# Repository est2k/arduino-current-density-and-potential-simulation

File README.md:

# arduino-current-density-and-potential-simulation
Potential and Current Density Simulation of Arduino Uno using FreeCAD, ElmerFEM and ParaView

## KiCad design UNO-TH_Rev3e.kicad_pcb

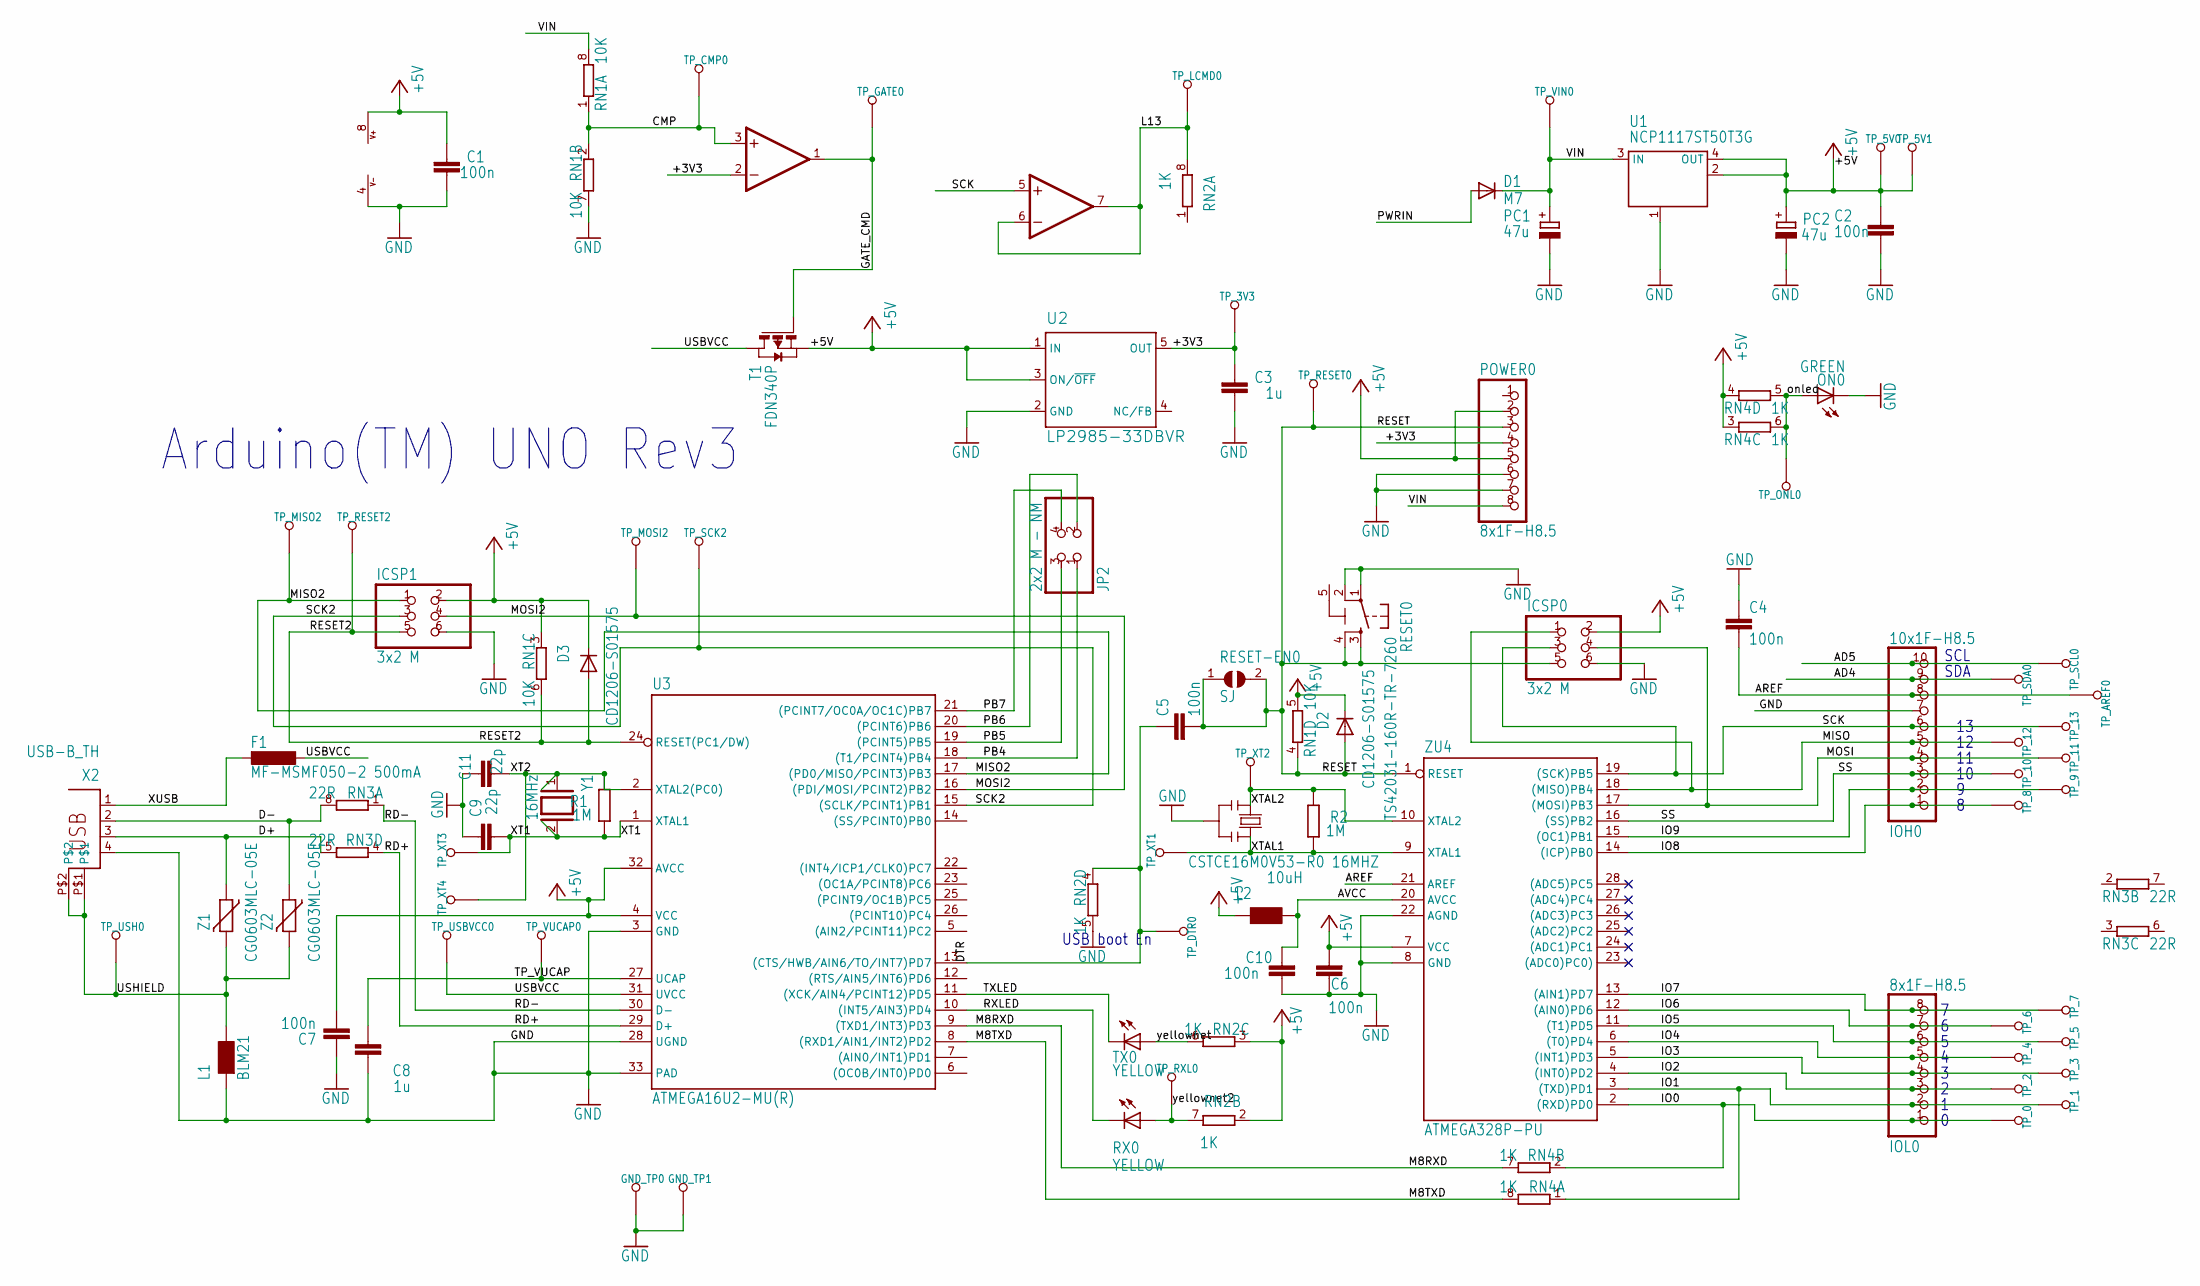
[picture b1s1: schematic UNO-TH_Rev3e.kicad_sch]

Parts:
C1, C2, C4, C5, C6, C7, C10: 100n; C0603-ROUND
C3, C8: 1u; C0603-ROUND
C9, C11: 22p; C0603-ROUND
D1: M7; SMB
D2, D3: CD1206-S01575; MINIMELF
F1: MF-MSMF050-2 500mA; L1812
GND_TP0, GND_TP1: TP_SP; TP-SP
ICSP0, ICSP1: 3x2 M; 2X03
IOH0: 10x1F-H8.5; 1X10
IOL0: 8x1F-H8.5; 1X08
JP2: 2x2 M - NM; 2X02
L1: BLM21; 0805
L2: 10uH; 0805
ON0: GREEN; CHIP-LED0805
PC1, PC2: 47u; PANASONIC_D
POWER0: 8x1F-H8.5; 1X08
R1, R2: 1M; R0603-ROUND
RESET0: TS42031-160R-TR-7260; TS42
RESET-EN0: SJ
RN1: 10K; CAY16
RN2, RN4: 1K; CAY16
RN3: 22R; CAY16
RX0: YELLOW; CHIP-LED0805
T1: FDN340P; SOT-23
TP_0, TP_1, TP_2, TP_3, TP_3V3, TP_4, TP_5, TP_5V0, TP_5V1, TP_6, TP_7, TP_8, TP_9, TP_10, TP_11, TP_12, TP_13: TP_SP; TP-SP
TP_AREF0: TP_SP; TP-SP
TP_CMP0: TP_SP; TP-SP
TP_DTR0: TP_SP; TP-SP
TP_GATE0: TP_SP; TP-SP
TP_LCMD0: TP_SP; TP-SP
TP_MISO2: TP_SP; TP-SP
TP_MOSI2: TP_SP; TP-SP
TP_ONL0: TP_SP; TP-SP
TP_RESET0, TP_RESET2: TP_SP; TP-SP
TP_RXL0: TP_SP; TP-SP
TP_SCK2: TP_SP; TP-SP
TP_SCL0: TP_SP; TP-SP
TP_SDA0: TP_SP; TP-SP
TP_USBVCC0: TP_SP; TP-SP
TP_USH0: TP_SP; TP-SP
TP_VIN0: TP_SP; TP-SP
TP_VUCAP0: TP_SP; TP-SP
TP_XT1, TP_XT2, TP_XT3, TP_XT4: TP_SP; TP-SP
TX0: YELLOW; CHIP-LED0805
U1: NCP1117ST50T3G; SOT223
U2: LP2985-33DBVR; SOT23-DBV
U3: ATMEGA16U2-MU(R); MLF32
U5: LMV358IDGKR; MSOP08
X2: USB-B_TH; PN61729
Y1: 16MHz; QS
Y2: CSTCE16M0V53-R0 16MHZ; RESONATOR
Z1, Z2: CG0603MLC-05E; CT_CN0603
ZU4: ATMEGA328P-PU; DIL28-3

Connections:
+5V: C1.2, C2.2, C6.2, C7.1, D2.C, D3.C, ICSP0.2, ICSP1.2, L2.1, PC2.+, POWER0.2, POWER0.5, RN1.3 (1), RN1.5 (2), RN2.2 (1), RN2.3 (1), RN4.3 (1), RN4.4 (1), T1.2 (S), TP_5V0.X (TESTP), TP_5V1.X (TESTP), U1.2 (OUT@1), U1.4 (OUT), U2.1 (IN), U2.3 (ON/~OFF), U3.4 (VCC), U3.32 (AVCC), U5.8 (V+), ZU4.7 (VCC)
/+3V3: C3.2, POWER0.4, TP_3V3.X (TESTP), U2.5 (OUT), U5.2 (-IN)
/AD4: IOH0.9, TP_SDA0.X (TESTP)
/AD5: IOH0.10, TP_SCL0.X (TESTP)
/AREF: C4.2, IOH0.8, TP_AREF0.X (TESTP), ZU4.21 (AREF)
/AVCC: C10.2, L2.2, ZU4.20 (AVCC)
/CMP: RN1.1, RN1.2 (1), TP_CMP0.X (TESTP), U5.3 (+IN)
/D+: RN3.5 (2), X2.3, Z1.1
/D-: RN3.8 (2), X2.2, Z2.1
/DTR: C5.1, RN2.4 (1), TP_DTR0.X (TESTP), U3.13 ((CTS/HWB/AIN6/TO/INT7)PD7)
/GATE_CMD: T1.3 (G), TP_GATE0.X (TESTP), U5.1 (OUT)
/IO0: IOL0.1, RN4.2 (1), TP_0.X (TESTP), ZU4.2 ((RXD)PD0)
/IO1: IOL0.2, RN4.1, TP_1.X (TESTP), ZU4.3 ((TXD)PD1)
/IO2: IOL0.3, TP_2.X (TESTP), ZU4.4 ((INT0)PD2)
/IO3: IOL0.4, TP_3.X (TESTP), ZU4.5 ((INT1)PD3)
/IO4: IOL0.5, TP_4.X (TESTP), ZU4.6 ((T0)PD4)
/IO5: IOL0.6, TP_5.X (TESTP), ZU4.11 ((T1)PD5)
/IO6: IOL0.7, TP_6.X (TESTP), ZU4.12 ((AIN0)PD6)
/IO7: IOL0.8, TP_7.X (TESTP), ZU4.13 ((AIN1)PD7)
/IO8: IOH0.1, TP_8.X (TESTP), ZU4.14 ((ICP)PB0)
/IO9: IOH0.2, TP_9.X (TESTP), ZU4.15 ((OC1)PB1)
/L13: RN2.8 (2), TP_LCMD0.X (TESTP), U5.6 (-IN), U5.7 (OUT)
/M8RXD: RN4.7 (2), U3.9 ((TXD1/INT3)PD3)
/M8TXD: RN4.8 (2), U3.8 ((RXD1/AIN1/INT2)PD2)
/MISO: ICSP0.1, IOH0.5, TP_12.X (TESTP), ZU4.18 ((MISO)PB4)
/MISO2: ICSP1.1, TP_MISO2.X (TESTP), U3.17 ((PD0/MISO/PCINT3)PB3)
/MOSI: ICSP0.4, IOH0.4, TP_11.X (TESTP), ZU4.17 ((MOSI)PB3)
/MOSI2: ICSP1.4, TP_MOSI2.X (TESTP), U3.16 ((PDI/MOSI/PCINT2)PB2)
/PB4: JP2.1, U3.18 ((T1/PCINT4)PB4)
/PB5: JP2.3, U3.19 ((PCINT5)PB5)
/PB6: JP2.2, U3.20 ((PCINT6)PB6)
/PB7: JP2.4, U3.21 ((PCINT7/OC0A/OC1C)PB7)
/PWRIN: D1.A
/RD+: RN3.4 (1), U3.29 (D+)
/RD-: RN3.1, U3.30 (D-)
/RESET: C5.2, D2.A, ICSP0.5, POWER0.3, RESET0.3, RESET0.4, RESET-EN0.1, RESET-EN0.2, RN1.4 (1), TP_RESET0.X (TESTP), ZU4.1 (RESET)
/RESET2: D3.A, ICSP1.5, RN1.6 (2), TP_RESET2.X (TESTP), U3.24 (RESET(PC1/DW))
/RXLED: RX0.C, U3.10 ((INT5/AIN3)PD4)
/SCK: ICSP0.3, IOH0.6, TP_13.X (TESTP), U5.5 (+IN), ZU4.19 ((SCK)PB5)
/SCK2: ICSP1.3, TP_SCK2.X (TESTP), U3.15 ((SCLK/PCINT1)PB1)
/SS: IOH0.3, TP_10.X (TESTP), ZU4.16 ((SS)PB2)
/TP_VUCAP: C8.1, TP_VUCAP0.X (TESTP), U3.27 (UCAP)
/TXLED: TX0.C, U3.11 ((XCK/AIN4/PCINT12)PD5)
/USBVCC: F1.1, T1.1 (D), TP_USBVCC0.X (TESTP), U3.31 (UVCC)
/USHIELD: L1.2, TP_USH0.X (TESTP), X2.P$1, X2.P$2, Z1.2, Z2.2
/VIN: D1.C, PC1.+, POWER0.8, RN1.8 (2), TP_VIN0.X (TESTP), U1.3 (IN)
/XT1: C9.1, R1.1, TP_XT3.X (TESTP), U3.1 (XTAL1), Y1.2
/XT2: C11.1, R1.2, TP_XT4.X (TESTP), U3.2 (XTAL2(PC0)), Y1.1
/XTAL1: R2.1, TP_XT1.X (TESTP), Y2.3, ZU4.9 (XTAL1)
/XTAL2: R2.2, TP_XT2.X (TESTP), Y2.1, ZU4.10 (XTAL2)
/XUSB: F1.2, X2.1
/onled: ON0.A, RN4.5 (2), RN4.6 (2), TP_ONL0.X (TESTP)
/yellownet: RN2.6 (2), TX0.A
/yellownet2: RN2.7 (2), RX0.A, TP_RXL0.X (TESTP)
GND: C1.1, C2.1, C3.1, C4.1, C6.1, C7.2, C8.2, C9.2, C10.1, C11.2, GND_TP0.X (TESTP), GND_TP1.X (TESTP), ICSP0.6, ICSP1.6, IOH0.7, L1.1, ON0.C, PC1.-, PC2.-, POWER0.6, POWER0.7, RESET0.1, RESET0.2, RN1.7 (2), RN2.5 (2), U1.1 (GND/ADJ), U2.2 (GND), U3.3 (GND), U3.28 (UGND), U3.33 (PAD), U5.4 (V-), X2.4, Y2.2, ZU4.8 (GND), ZU4.22 (AGND)

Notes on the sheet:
SDA
SCL
Arduino(TM) UNO Rev3
USB boot En

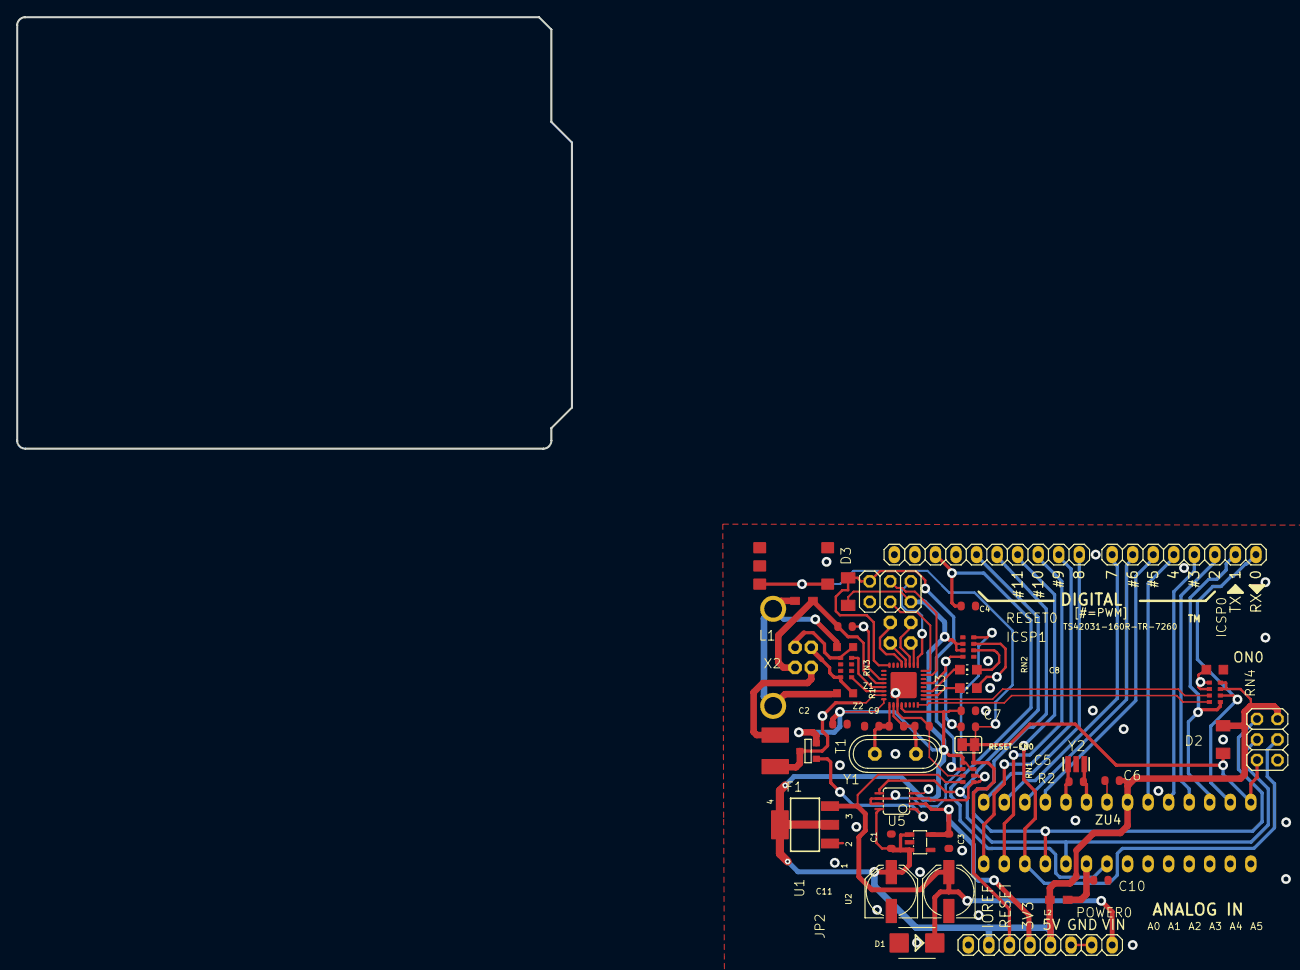
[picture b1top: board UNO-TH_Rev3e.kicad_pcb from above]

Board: 2 copper layers, 68.6 x 53.3 mm, 88 parts (0 on the bottom side), 54 nets.
